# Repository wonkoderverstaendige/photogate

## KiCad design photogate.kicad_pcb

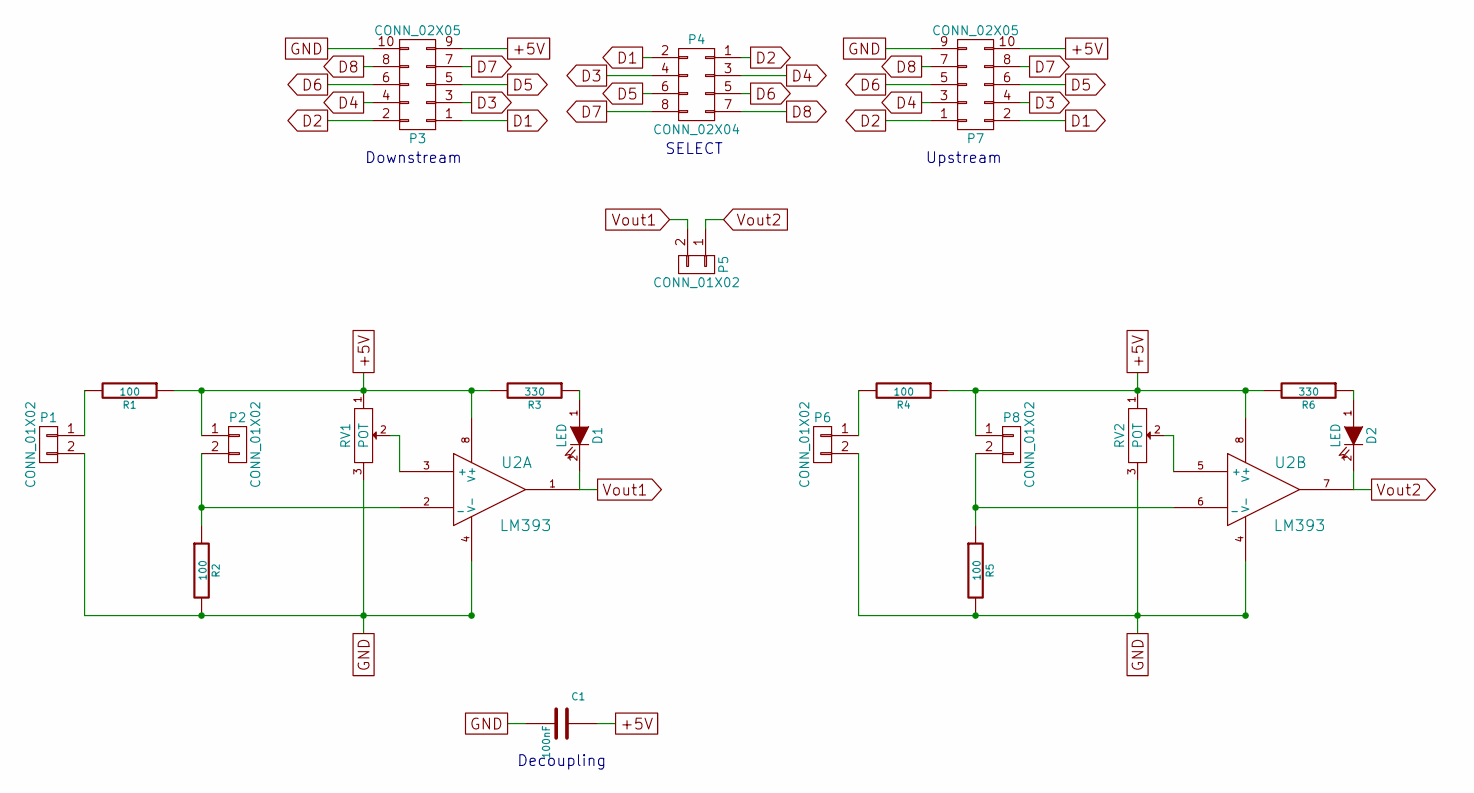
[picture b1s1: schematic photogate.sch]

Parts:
C1: 100nF; SMD-1206
D1, D2: LED; LED-1206
P1, P2, P6, P8: CONN_01X02; Socket_Strip_Angled_1x02
P3, P7: CONN_02X05; Wurth_2x05_HEADER_STRAIGHT
P4: CONN_02X04; Socket_Strip_Straight_2x04
P5: CONN_01X02; Socket_Strip_Straight_1x02
R1, R2, R4, R5: 100; R_1206
R3, R6: 330; R_1206
RV1, RV2: POT; PVZ2A
U2: LM393; DIP-8__300

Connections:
+5V: C1.1, P2.1, P3.9, P7.10, P8.1, R1.1, R3.2, R4.1, R6.2, RV1.1, RV2.1, U2.8 (V+)
D1: P3.1, P4.2, P7.2
D2: P3.2, P4.1, P7.1
D3: P3.3, P4.4, P7.4
D4: P3.4, P4.3, P7.3
D5: P3.5, P4.6, P7.6
D6: P3.6, P4.5, P7.5
D7: P3.7, P4.8, P7.8
D8: P3.8, P4.7, P7.7
GND: C1.2, P1.2, P3.10, P6.2, P7.9, R2.2, R5.2, RV1.3, RV2.3, U2.4 (V-)
unnamed: D1.1 (A), R3.1
unnamed: D2.1 (A), R6.1
unnamed: P1.1, R1.2
unnamed: P2.2, R2.1, U2.2 (_)
unnamed: P6.1, R4.2
unnamed: P8.2, R5.1, U2.6 (_)
unnamed: RV1.2, U2.3 (+)
unnamed: RV2.2, U2.5 (+)
Vout1: D1.2 (K), P5.2, U2.1
Vout2: D2.2 (K), P5.1, U2.7

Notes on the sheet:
Upstream
Downstream
SELECT
Decoupling

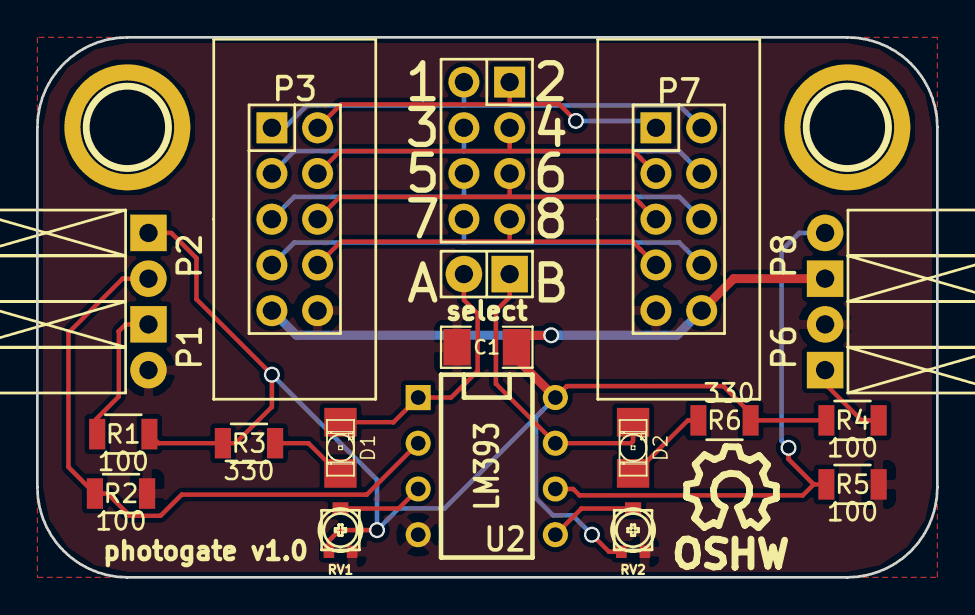
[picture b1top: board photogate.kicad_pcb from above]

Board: 2 copper layers, 50.0 x 30.0 mm, 23 parts (0 on the bottom side), 20 nets.

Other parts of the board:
1PIN, 1PIN#2: P***; 1pin
SYM: Symbol_OSHW-Logo_SilkScreen_07Jul2012; Symbol_OSHW-Logo_SilkScreen

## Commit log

2014-09-25 Flipped flat cable connector
2014-09-25 Add .gitignore for kicad stuff
2014-09-25 Readme and todo list
2014-09-26 Rebuild layout w/ updated footprints
